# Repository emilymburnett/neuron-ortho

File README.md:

# Zen - an ortho PCB designed for the Neuron

Zephyraeon's first PCB, not even sure it's functional yet so use at your own risk.

Any feedback welcome, very willing to learn :)

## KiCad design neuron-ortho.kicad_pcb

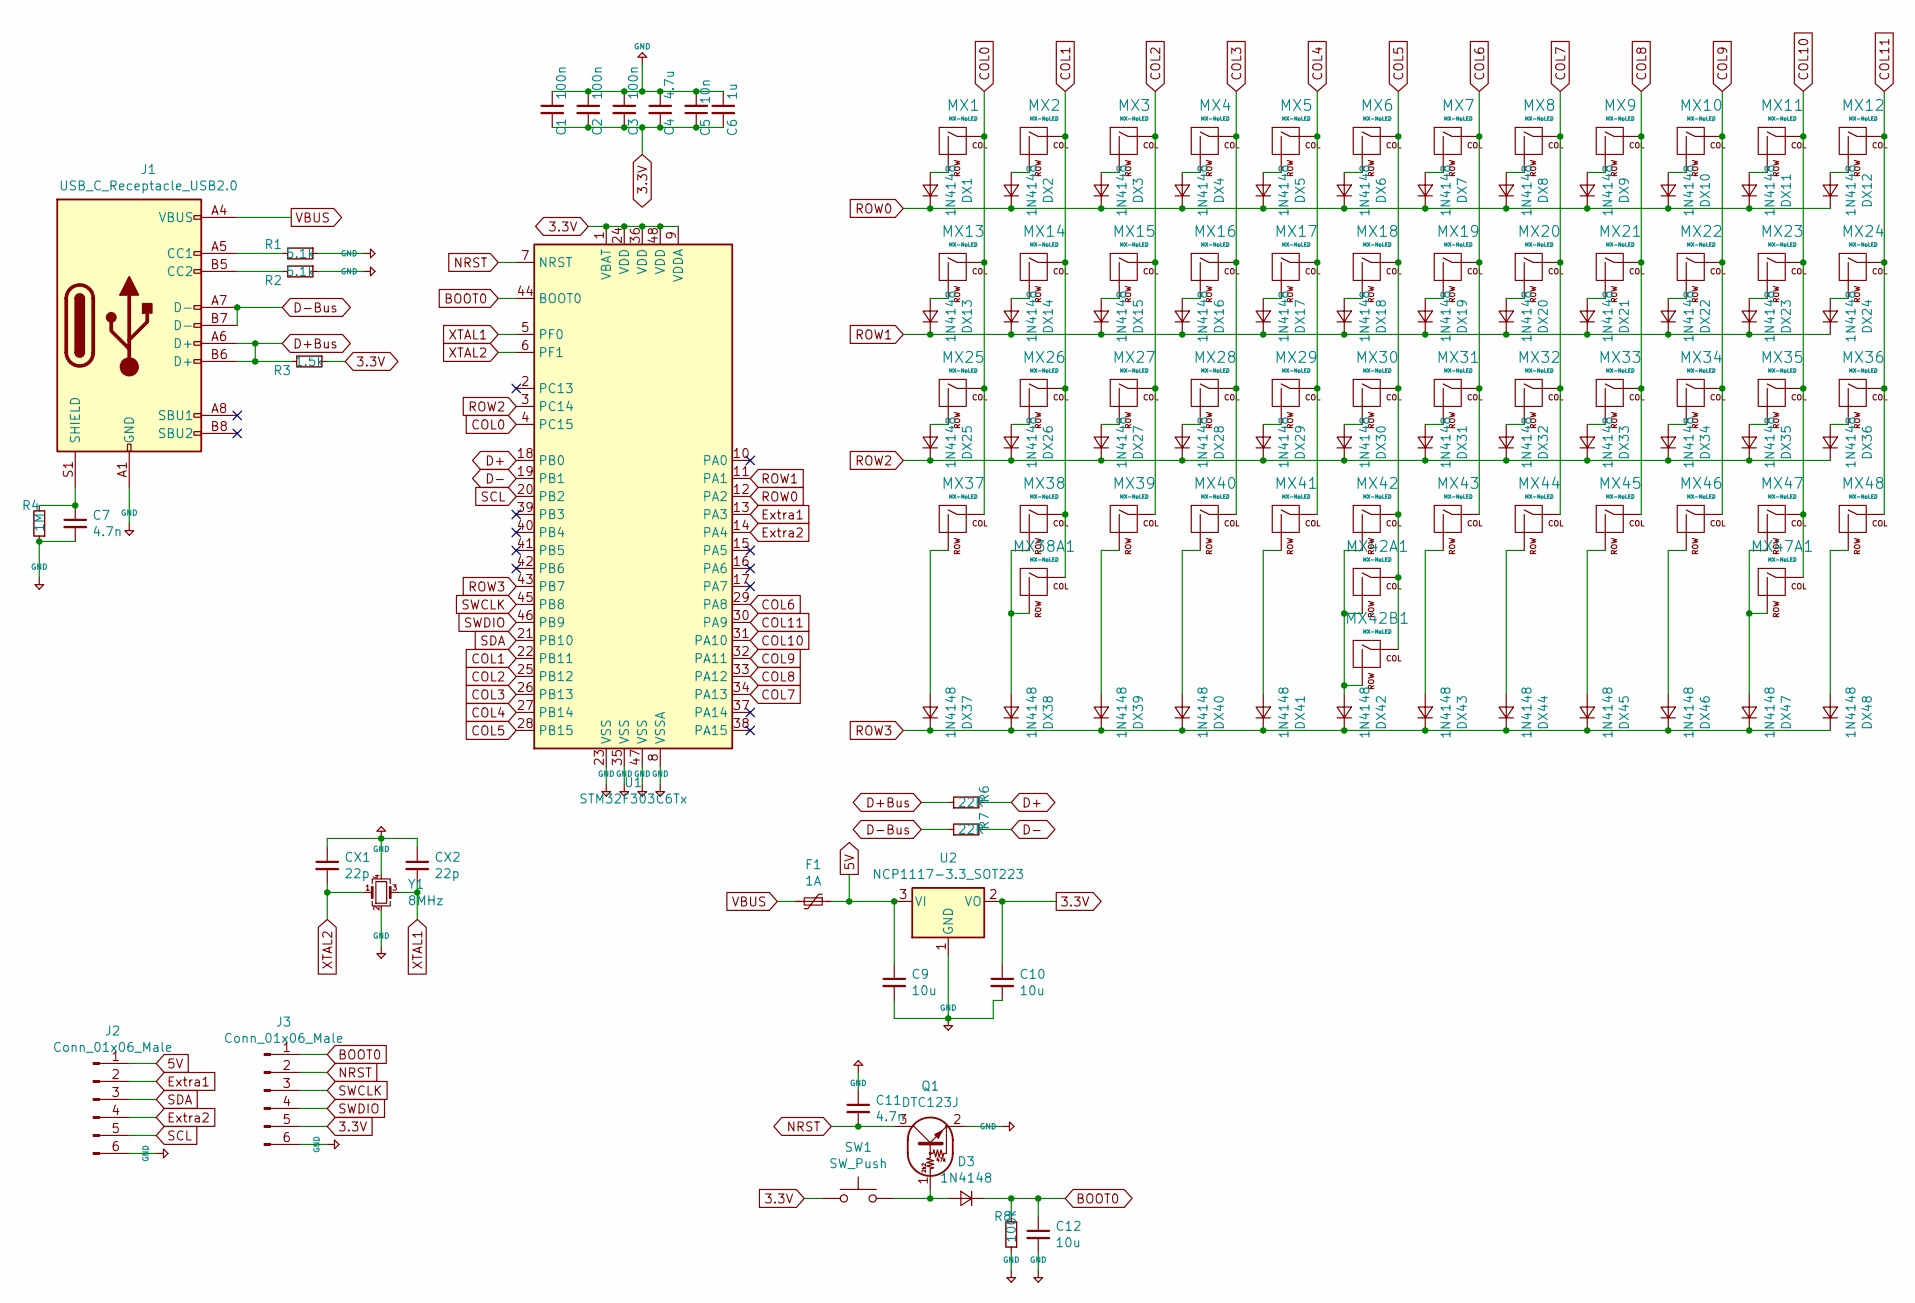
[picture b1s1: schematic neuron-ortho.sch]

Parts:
C1, C2, C3: 100n; C_0805_2012Metric
C4: 4.7u; C_0805_2012Metric
C5: 10n; C_0805_2012Metric
C6: 1u; C_0805_2012Metric
C7, C11: 4.7n; C_0805_2012Metric
C9, C10, C12: 10u; C_0805_2012Metric
CX1, CX2: 22p; C_0805_2012Metric
D3: 1N4148; D_SOD-123
DX1, DX2, DX3, DX4, DX5, DX6, DX7, DX8, DX9, DX10, DX11, DX12, DX13, DX14, DX15, DX16, DX17, DX18, DX19, DX20, DX21, DX22, DX23, DX24, DX25, DX26, DX27, DX28, DX29, DX30, DX31, DX32, DX33, DX34, DX35, DX36, DX37, DX38, DX39, DX40, DX41, DX42, DX43, DX44, DX45, DX46, DX47, DX48: 1N4148; D_SOD-123
F1: 1A; Fuse_1206_3216Metric
J1: USB_C_Receptacle_USB2.0; USB_C_Receptacle_GCT_USB4085
J2, J3: Conn_01x06_Male; Reset_Pretty
MX1, MX2, MX3, MX4, MX5, MX6, MX7, MX8, MX9, MX10, MX11, MX12, MX13, MX14, MX15, MX16, MX17, MX18, MX19, MX20, MX21, MX22, MX23, MX24, MX25, MX26, MX27, MX28, MX29, MX30, MX31, MX32, MX33, MX34, MX35, MX36, MX37, MX38, MX39, MX40, MX41, MX42, MX43, MX44, MX45, MX46, MX47, MX48: MX-NoLED; MX-1U-NoLED
MX38A1, MX47A1: MX-NoLED; MX-1.5U-NoLED
MX42A1: MX-NoLED; MX-7U-ReversedStabilizers-NoLED
MX42B1: MX-NoLED; MX-2U-ReversedStabilizers-NoLED
Q1: DTC123J; SOT-23
R1, R2: 5.1k; R_0805_2012Metric
R3: 1.5k; R_0805_2012Metric
R4: 1M; R_0805_2012Metric
R6, R7: 22R; R_0805_2012Metric
R8: 100k; R_0805_2012Metric
SW1: SW_Push; SKQG-1155865
U1: STM32F303C6Tx; LQFP-48_7x7mm_P0.5mm
U2: NCP1117-3.3_SOT223; SOT-223-3_TabPin2
Y1: 8MHz; Crystal_SMD_3225-4Pin_3.2x2.5mm

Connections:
3.3V: C1.2, C2.2, C3.2, C4.2, C5.1, C6.2, C10.1, J3.5, R3.1, SW1.1, U1.1 (VBAT), U1.9 (VDDA), U1.24 (VDD), U1.36 (VDD), U1.48 (VDD), U2.2 (VO)
5V: C9.1, F1.1, J2.1, U2.3 (VI)
+5V: C1.1, C2.1, C3.1, C4.1, C5.2, C6.1, C7.2, C9.2, C10.2, C11.1, C12.2, CX1.1, CX2.1, J1.A1 (GND), J1.A12 (GND), J1.B1 (GND), J1.B12 (GND), J2.6, J3.6, Q1.2 (E), R1.1, R2.1, R4.1, R8.1, U1.8 (VSSA), U1.23 (VSS), U1.35 (VSS), U1.47 (VSS), U2.1 (GND), Y1.2, Y1.4
BOOT0: C12.1, D3.1 (K), J3.1, R8.2, U1.44 (BOOT0)
COL0: MX1.1 (COL), MX13.1 (COL), MX25.1 (COL), MX37.1 (COL), U1.4 (PC15)
COL1: MX2.1 (COL), MX14.1 (COL), MX26.1 (COL), MX38.1 (COL), MX38A1.1 (COL), U1.22 (PB11)
COL2: MX3.1 (COL), MX15.1 (COL), MX27.1 (COL), MX39.1 (COL), U1.25 (PB12)
COL3: MX4.1 (COL), MX16.1 (COL), MX28.1 (COL), MX40.1 (COL), U1.26 (PB13)
COL4: MX5.1 (COL), MX17.1 (COL), MX29.1 (COL), MX41.1 (COL), U1.27 (PB14)
COL5: MX6.1 (COL), MX18.1 (COL), MX30.1 (COL), MX42.1 (COL), MX42A1.1 (COL), MX42B1.1 (COL), U1.28 (PB15)
COL6: MX7.1 (COL), MX19.1 (COL), MX31.1 (COL), MX43.1 (COL), U1.29 (PA8)
COL7: MX8.1 (COL), MX20.1 (COL), MX32.1 (COL), MX44.1 (COL), U1.34 (PA13)
COL8: MX9.1 (COL), MX21.1 (COL), MX33.1 (COL), MX45.1 (COL), U1.33 (PA12)
COL9: MX10.1 (COL), MX22.1 (COL), MX34.1 (COL), MX46.1 (COL), U1.32 (PA11)
COL10: MX11.1 (COL), MX23.1 (COL), MX35.1 (COL), MX47.1 (COL), MX47A1.1 (COL), U1.31 (PA10)
COL11: MX12.1 (COL), MX24.1 (COL), MX36.1 (COL), MX48.1 (COL), U1.30 (PA9)
D+: R6.2, U1.18 (PB0)
D+Bus: J1.A6 (D+), J1.B6 (D+), R3.2, R6.1
D-: R7.2, U1.19 (PB1)
D-Bus: J1.A7 (D-), J1.B7 (D-), R7.1
Extra1: J2.2, U1.13 (PA3)
Extra2: J2.4, U1.14 (PA4)
NRST: C11.2, J3.2, Q1.3 (C), U1.7 (NRST)
unnamed: C7.1, J1.S1 (SHIELD), R4.2
unnamed: D3.2 (A), Q1.1 (B), SW1.2
unnamed: DX1.2 (A), MX1.2 (ROW)
unnamed: DX2.2 (A), MX2.2 (ROW)
unnamed: DX3.2 (A), MX3.2 (ROW)
unnamed: DX4.2 (A), MX4.2 (ROW)
unnamed: DX5.2 (A), MX5.2 (ROW)
unnamed: DX6.2 (A), MX6.2 (ROW)
unnamed: DX7.2 (A), MX7.2 (ROW)
unnamed: DX8.2 (A), MX8.2 (ROW)
unnamed: DX9.2 (A), MX9.2 (ROW)
unnamed: DX10.2 (A), MX10.2 (ROW)
unnamed: DX11.2 (A), MX11.2 (ROW)
unnamed: DX12.2 (A), MX12.2 (ROW)
unnamed: DX13.2 (A), MX13.2 (ROW)
unnamed: DX14.2 (A), MX14.2 (ROW)
unnamed: DX15.2 (A), MX15.2 (ROW)
unnamed: DX16.2 (A), MX16.2 (ROW)
unnamed: DX17.2 (A), MX17.2 (ROW)
unnamed: DX18.2 (A), MX18.2 (ROW)
unnamed: DX19.2 (A), MX19.2 (ROW)
unnamed: DX20.2 (A), MX20.2 (ROW)
unnamed: DX21.2 (A), MX21.2 (ROW)
unnamed: DX22.2 (A), MX22.2 (ROW)
unnamed: DX23.2 (A), MX23.2 (ROW)
unnamed: DX24.2 (A), MX24.2 (ROW)
unnamed: DX25.2 (A), MX25.2 (ROW)
unnamed: DX26.2 (A), MX26.2 (ROW)
unnamed: DX27.2 (A), MX27.2 (ROW)
unnamed: DX28.2 (A), MX28.2 (ROW)
unnamed: DX29.2 (A), MX29.2 (ROW)
unnamed: DX30.2 (A), MX30.2 (ROW)
unnamed: DX31.2 (A), MX31.2 (ROW)
unnamed: DX32.2 (A), MX32.2 (ROW)
unnamed: DX33.2 (A), MX33.2 (ROW)
unnamed: DX34.2 (A), MX34.2 (ROW)
unnamed: DX35.2 (A), MX35.2 (ROW)
unnamed: DX36.2 (A), MX36.2 (ROW)
unnamed: DX37.2 (A), MX37.2 (ROW)
unnamed: DX38.2 (A), MX38.2 (ROW), MX38A1.2 (ROW)
unnamed: DX39.2 (A), MX39.2 (ROW)
unnamed: DX40.2 (A), MX40.2 (ROW)
unnamed: DX41.2 (A), MX41.2 (ROW)
unnamed: DX42.2 (A), MX42.2 (ROW), MX42A1.2 (ROW), MX42B1.2 (ROW)
unnamed: DX43.2 (A), MX43.2 (ROW)
unnamed: DX44.2 (A), MX44.2 (ROW)
unnamed: DX45.2 (A), MX45.2 (ROW)
unnamed: DX46.2 (A), MX46.2 (ROW)
unnamed: DX47.2 (A), MX47.2 (ROW), MX47A1.2 (ROW)
unnamed: DX48.2 (A), MX48.2 (ROW)
unnamed: J1.A5 (CC1), R1.2
unnamed: J1.B5 (CC2), R2.2
ROW0: DX1.1 (K), DX2.1 (K), DX3.1 (K), DX4.1 (K), DX5.1 (K), DX6.1 (K), DX7.1 (K), DX8.1 (K), DX9.1 (K), DX10.1 (K), DX11.1 (K), DX12.1 (K), U1.12 (PA2)
ROW1: DX13.1 (K), DX14.1 (K), DX15.1 (K), DX16.1 (K), DX17.1 (K), DX18.1 (K), DX19.1 (K), DX20.1 (K), DX21.1 (K), DX22.1 (K), DX23.1 (K), DX24.1 (K), U1.11 (PA1)
ROW2: DX25.1 (K), DX26.1 (K), DX27.1 (K), DX28.1 (K), DX29.1 (K), DX30.1 (K), DX31.1 (K), DX32.1 (K), DX33.1 (K), DX34.1 (K), DX35.1 (K), DX36.1 (K), U1.3 (PC14)
ROW3: DX37.1 (K), DX38.1 (K), DX39.1 (K), DX40.1 (K), DX41.1 (K), DX42.1 (K), DX43.1 (K), DX44.1 (K), DX45.1 (K), DX46.1 (K), DX47.1 (K), DX48.1 (K), U1.43 (PB7)
SCL: J2.5, U1.20 (PB2)
SDA: J2.3, U1.21 (PB10)
SWCLK: J3.3, U1.45 (PB8)
SWDIO: J3.4, U1.46 (PB9)
VBUS: F1.2, J1.A4 (VBUS), J1.A9 (VBUS), J1.B4 (VBUS), J1.B9 (VBUS)
XTAL1: CX2.2, U1.5 (PF0), Y1.3
XTAL2: CX1.2, U1.6 (PF1), Y1.1

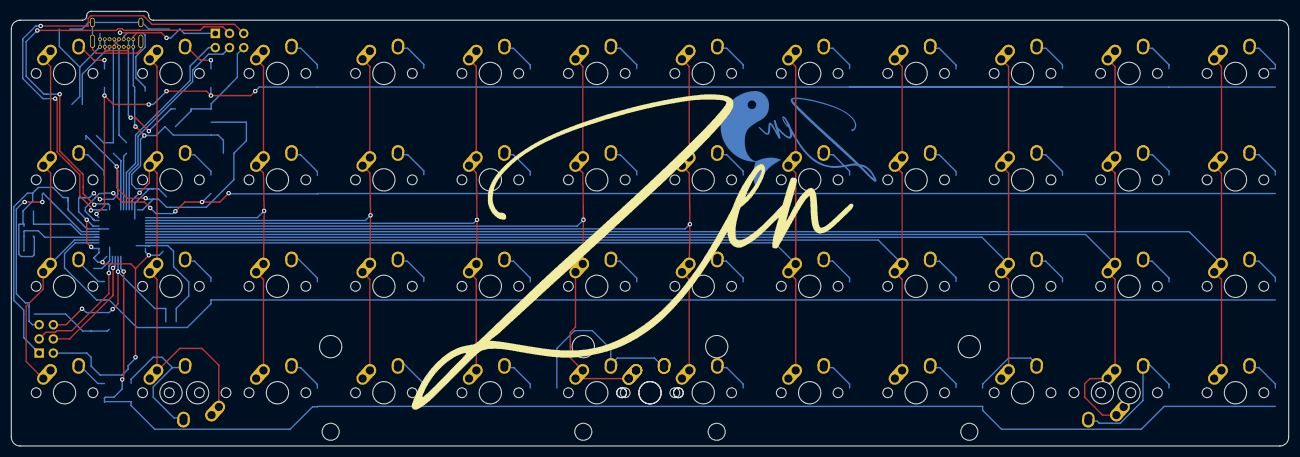
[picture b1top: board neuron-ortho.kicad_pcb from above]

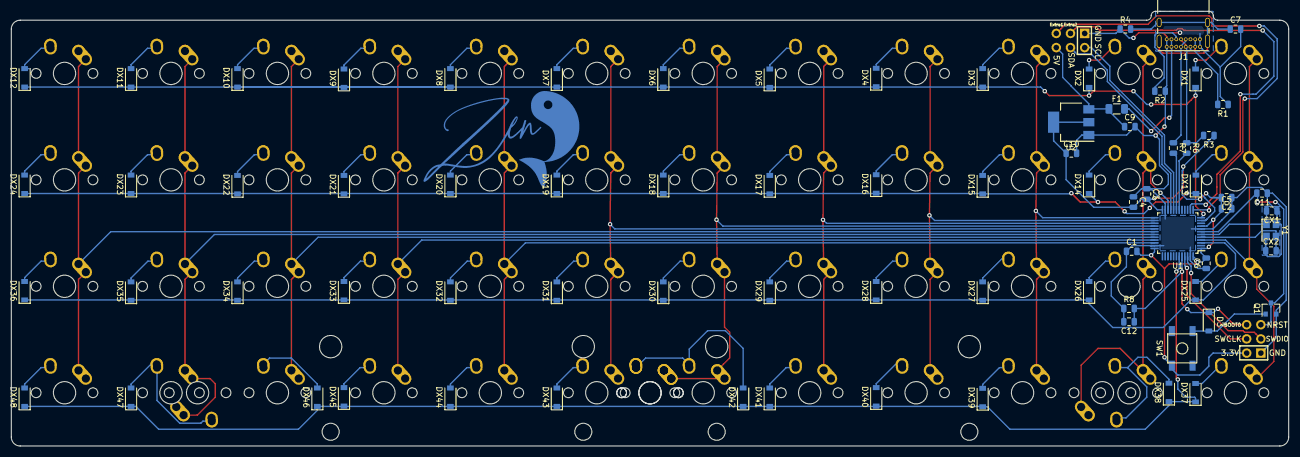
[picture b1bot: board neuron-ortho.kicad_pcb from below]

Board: 2 copper layers, 228.6 x 77.8 mm, 133 parts (81 on the bottom side), 86 nets.

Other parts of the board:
G2: LOGO; PCBlogoZen
G3, G3#2: LOGO; PCBlogoKoiFlipped

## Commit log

2020-03-14 Creation of kicad project
2020-03-14 Add submodules
2020-03-14 Added project libraries
2020-03-14 ATmega schema partially complete
2020-03-14 Add digikey library
2020-03-15 Schema updated with ESD protection etc
2020-03-15 Updated schema values
    Need to do switch matrix
2020-03-15 Added Switch matrix
2020-03-15 Assigned some MCU pins
2020-03-15 Added keymap image
2020-03-16 Completed PCB trace
2020-03-17 Deleted traces, move component placing
    Got some tips from Xelus and started over with component placement. New traces next
2020-03-18 Finished non-switch matrix traces
2020-03-18 Switch matrix traces done
2020-03-18 Tidied traces, added logo
2020-03-18 Added license
2020-03-18 Updated schema
2020-03-18 Updated pin out footprint
2020-03-18 Added missing trace
